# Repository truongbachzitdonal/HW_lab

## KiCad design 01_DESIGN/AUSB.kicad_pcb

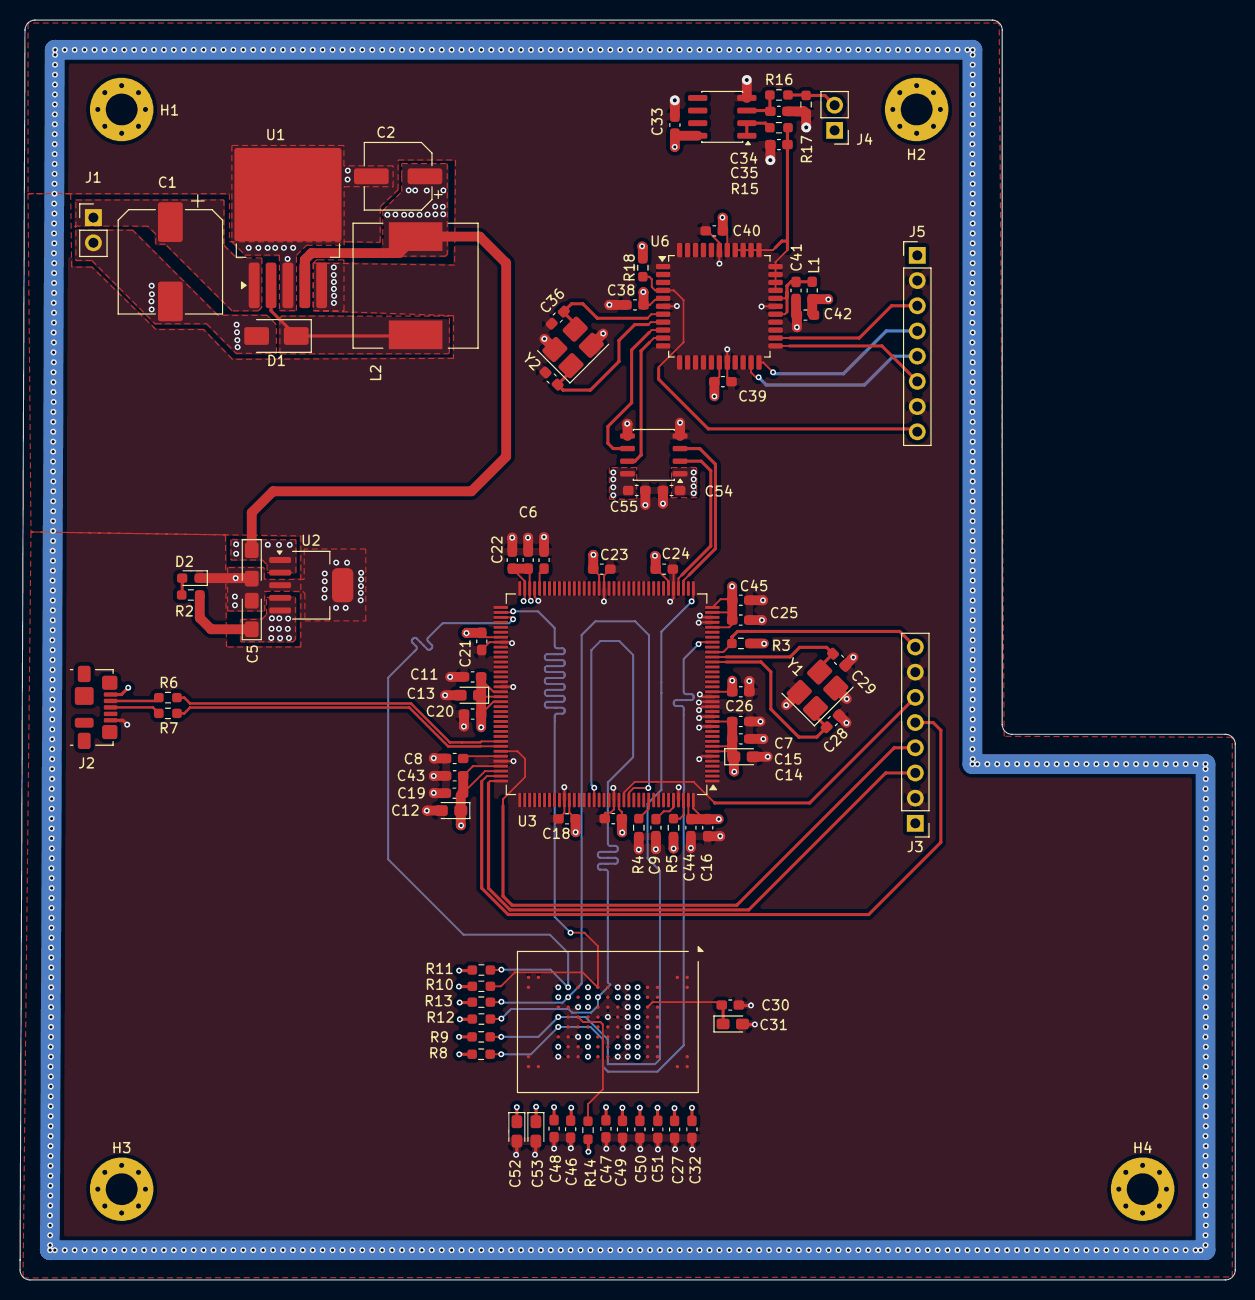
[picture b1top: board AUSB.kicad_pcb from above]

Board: 4 copper layers, 122.5 x 127.0 mm, 93 parts (0 on the bottom side), 47 nets.

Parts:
C1: 680uF; CP_Elec_10x10
C2: 220uF; CP_Elec_6.3x7.7
C4, C5: 10uF/16V; CP_EIA-3216-18_Kemet-A_HandSolder
C6, C7, C11, C15, C16, C17, C18, C19, C20, C21, C22, C23, C24, C25, C26, C27, C30, C32, C33, C34, C35, C38, C39, C40, C41, C42, C43, C44, C45, C46, C47, C48, C49, C50, C51, C54, C55: 0.1uF/6.3V; C_0603_1608Metric_Pad1.08x0.95mm_HandSolder
C8, C9, C10: 4.7uF/6.3V; C_0603_1608Metric_Pad1.08x0.95mm_HandSolder
C12, C13, C52, C53: 4.7uF/6.3V; CP_EIA-2012-12_Kemet-R_HandSolder
C14: 10uF/10V; CP_EIA-2012-12_Kemet-R_HandSolder
C28, C29, C36, C37: 16pF/6.3V; C_0603_1608Metric_Pad1.08x0.95mm_HandSolder
C31: 1uF/6.3V; CP_EIA-2012-12_Kemet-R_HandSolder
D1: SS34; D_SMA
D2: 150060YS75000; LED_0603_1608Metric_Pad1.05x0.95mm_HandSolder
H1, H2, H3, H4: M3; MountingHole_3.2mm_M3_Pad_Via
J1, J4: JP2; PinHeader_1x02_P2.54mm_Vertical
J2: 0473460001; USB_Micro-B_Molex_47346-0001
J3, J5: JP8; PinHeader_1x08_P2.54mm_Vertical
L1: 10uH/250mA; L_0603_1608Metric_Pad1.05x0.95mm_HandSolder
L2: 33uH; L_12x12mm_H6mm
R2: 1k; R_0603_1608Metric_Pad0.98x0.95mm_HandSolder
R3, R4, R5, R14, R18: 4.7k; R_0603_1608Metric_Pad0.98x0.95mm_HandSolder
R6, R7: 0R/DNP; R_0603_1608Metric_Pad0.98x0.95mm_HandSolder
R8, R9, R10, R11, R12, R13, R17: 10k; R_0603_1608Metric_Pad0.98x0.95mm_HandSolder
R15, R16: 22R; R_0603_1608Metric_Pad0.98x0.95mm_HandSolder
U1: LM2596S-5; TO-263-5_TabPin3
U2: TPS7A4533DCQR; SOT-223-6
U3: STM32H745ZIT3; LQFP-144_20x20mm_P0.5mm
U4: ISO7721DR; JEITA_SOIC-8_3.9x4.9mm_P1.27mm
U5: OPA2340; SOIC-8_3.9x4.9mm_P1.27mm
U6: ATMEGA324PA; TQFP-44_10x10mm_P0.8mm
U7: MTFC32GAZAQDW-AAT; BGA-100_14x18mm_Layout10x17_P1mm
Y1, Y2: ECS-250-12-33Q-JES-TR; Crystal_SMD_3225-4Pin_3.2x2.5mm_HandSoldering

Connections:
+3.3V: C5.1, C6.1, C7.1, C11.1, C12.1, C13.1, C14.1, C15.1, C16.1, C17.1, C18.1, C19.1, C20.1, C21.1, C22.1, C23.1, C24.1, C25.1, C26.1, C27.1, C32.1, C43.1, C44.1, C45.1, C46.1, C47.1, C48.1, C49.1, C50.1, C51.1, C52.1, C53.1, C54.1, J3.1, R2.1, R3.2, R5.2, R8.1, R9.1, R10.1, R11.1, R12.1, R13.1, R14.2, U2.4 (OUT), U2.5 (SENSE), U3.7 (VDD), U3.8 (VBAT), U3.13 (VDD), U3.19 (VDD), U3.32 (VDD), U3.35 (VREF+), U3.36 (VDDA), U3.42 (VDD), U3.56 (VDD), U3.70 (VDDLDO), U3.71 (VDD), U3.79 (VDD), U3.90 (VDD50USB), U3.91 (VDD33USB), U3.92 (VDD), U3.105 (VDDLDO), U3.106 (VDD), U3.119 (VDD), U3.129 (VDD), U3.143 (VDDLDO), U3.144 (VDD), U4.1 (VCC1), U7.F2 (VCC), U7.F3 (VCC), U7.F4 (VCC), U7.F5 (VCC), U7.F6 (VCC), U7.F7 (VCC), U7.F8 (VCC), U7.F9 (VCC), U7.H3 (VCCQ), U7.H8 (VCCQ), U7.L2 (VCCQ), U7.L4 (VCCQ), U7.L7 (VCCQ), U7.L9 (VCCQ), U7.P3 (VCCQ), U7.P8 (VCCQ)
+5V: C2.1, C4.1, C33.1, C38.1, C39.1, C40.1, C42.1, C55.1, J2.1 (VBUS), J4.1, J5.1, L1.2, L2.2, R18.2, U1.4 (FB), U2.1 (~SHDN), U2.2 (IN), U4.8 (VCC2), U5.8 (V+), U6.5 (VCC), U6.17 (VCC), U6.38 (VCC)
+12V: C1.1, J1.1, U1.1 (VIN)
/04_POWER/SHIELDING: H1.1 (1_1), H2.1 (1_1), H3.1 (1_1), H4.1 (1_1)
/05_MCU/MCU_BOOT0: R4.2, U3.135 (BOOT0)
/05_MCU/MCU_JTAG_TCK: J3.5, U3.107 (PA14)
/05_MCU/MCU_JTAG_TDI: J3.3, U3.108 (PA15)
/05_MCU/MCU_JTAG_TDO: J3.6, U3.130 (PB3)
/05_MCU/MCU_JTAG_TMS: J3.4, U3.102 (PA13)
/05_MCU/MCU_JTAG_nRESET: J3.8, R3.1, U3.27 (~RST)
/05_MCU/MCU_OSCIN: C28.1, U3.25 (PH0-OSC_IN), Y1.1 (IN/OUT)
/05_MCU/MCU_OSCOUT: C29.1, U3.26 (PH1-OSC_OUT), Y1.3 (OUT/IN)
/05_MCU/MCU_PDR: R5.1, U3.142 (PDR_ON)
/05_MCU/MCU_VCAP1: C10.1, U3.68 (VCAP)
/05_MCU/MCU_VCAP2: C8.1, U3.103 (VCAP)
/05_MCU/MCU_VCAP3: C9.1, U3.140 (VCAP)
/05_MCU/USB_2.0_CONN_N: J2.2 (D-), R6.1
/05_MCU/USB_2.0_CONN_P: J2.3 (D+), R7.1
/05_MCU/USB_2.0_D_N: R6.2, U3.100 (PA11)
/05_MCU/USB_2.0_D_P: R7.2, U3.101 (PA12)
/06_eMMC/EMMC2_nRST: R14.1, U7.M5 (RST_n)
/07_AVR/ADC_TEMP1: C34.1, R15.1, U6.30 (PA7_(ADC7/PCINT7)), U6.31 (PA6_(ADC6/PCINT6)), U6.32 (PA5_(ADC5/PCINT5)), U6.33 (PA4_(ADC4/PCINT4)), U6.34 (PA3_(ADC3/PCINT3)), U6.35 (PA2_(ADC2/PCINT2)), U6.36 (PA1_(ADC1/PCINT1)), U6.37 (PA0_(ADC0/PCINT0))
/07_AVR/AVR_JTAG_TCK: J5.5, U6.21 (PC2_(PCINT18/TCK))
/07_AVR/AVR_JTAG_TDI: J5.3, U6.24 (PC5_(TDI/PCINT21))
/07_AVR/AVR_JTAG_TDO: J5.6, U6.23 (PC4_(TDO/PCINT20))
/07_AVR/AVR_JTAG_TMS: J5.4, U6.22 (PC3_(PCINT19/TMS))
/07_AVR/AVR_JTAG_nRESET: J5.8, R18.1, U6.4 (~RESET)
/07_AVR/NTC1-: J4.2, R16.2, R17.2
AVR_ISO_UART0_RX: U4.6 (OUTB), U6.9 (PD0_(PCINT24/RXD0/T3))
AVR_ISO_UART0_TX: U4.7 (INA), U6.10 (PD1_(PCINT25/TXD0))
GND: C1.2, C2.2, C4.2, C5.2, C6.2, C7.2, C8.2, C9.2, C10.2, C11.2, C12.2, C13.2, C14.2, C15.2, C16.2, C17.2, C18.2, C19.2, C20.2, C21.2, C22.2, C23.2, C24.2, C25.2, C26.2, C27.2, C28.2, C29.2, C30.2, C31.2, C32.2, C33.2, C34.2, C35.2, C36.2, C37.2, C38.2, C39.2, C40.2, C41.2, C42.2, C43.2, C44.2, C45.2, C46.2, C47.2, C48.2, C49.2, C50.2, C51.2, C52.2, C53.2, C54.2, C55.2, D1.2 (A), D2.1 (K), J1.2, J2.5 (GND), J3.2, J3.7, J5.2, J5.7, R4.1, R17.1, U1.3 (GND), U1.5 (~ON/OFF), U2.3 (GND), U2.6 (GND), U3.6 (VSS), U3.12 (VSS), U3.14 (VSSSMPS), U3.16 (VDDSMPS), U3.17 (VFBSMPS), U3.18 (VSS), U3.33 (VSS), U3.34 (VSSA), U3.41 (VSS), U3.55 (VSS), U3.69 (VSS), U3.80 (VSS), U3.89 (VSS), U3.104 (VSS), U3.118 (VSS), U3.128 (VSS), U3.141 (VSS), U4.4 (GND1), U4.5 (GND2), U5.4 (V-), U6.6 (GND), U6.18 (GND), U6.28 (GND), U6.39 (GND), U7.G2 (VSS), U7.G3 (VSS), U7.G4 (VSS), U7.G5 (VSS), U7.G6 (VSS), U7.G7 (VSS), U7.G8 (VSS), U7.G9 (VSS), U7.H2 (VSSQ), U7.H9 (VSSQ), U7.J5 (VSS), U7.L3 (VSSQ), U7.L8 (VSSQ), U7.M4 (VSSQ), U7.M7 (VSSQ), U7.P2 (VSSQ), U7.P9 (VSSQ), Y1.2 (GND), Y1.4 (GND), Y2.2 (GND), Y2.4 (GND)
MCU_ISO_UART2_RX: U3.40 (PA3), U4.2 (OUTA)
MCU_ISO_UART2_TX: U3.39 (PA2), U4.3 (INB)
MCU_eMMC_SDMMC2_CK: R8.2, U3.29 (PC1), U7.P6 (CLK)
MCU_eMMC_SDMMC2_CMD: R9.2, U3.37 (PA0), U7.P5 (CMD)
MCU_eMMC_SDMMC2_D0: R10.2, U3.74 (PB14), U7.K2 (DAT0)
MCU_eMMC_SDMMC2_D1: R11.2, U3.75 (PB15), U7.N2 (DAT1)
MCU_eMMC_SDMMC2_D2: R12.2, U3.124 (PG11), U7.K3 (DAT2)
MCU_eMMC_SDMMC2_D3: R13.2, U3.131 (PB4), U7.N3 (DAT3)
unnamed: D1.1 (K), L2.1, U1.2 (OUT)
unnamed: D2.2 (A), R2.2
unnamed: C35.1, R16.1, U5.3 (+)
unnamed: R15.2, U5.1, U5.2 (-)
unnamed: C41.1, L1.1, U6.27 (AVCC), U6.29 (AREF)
unnamed: C37.1, U6.8 (XTAL1), Y2.1 (IN/OUT)
unnamed: C36.1, U6.7 (XTAL2), Y2.3 (OUT/IN)
unnamed: C30.1, C31.1, U7.E4 (VDDIM)
